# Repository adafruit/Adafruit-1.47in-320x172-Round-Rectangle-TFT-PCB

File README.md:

## Adafruit Adafruit 1.47" 320x172 Round Rectangle Color IPS TFT Display - ST7789 PCB

<a href="http://www.adafruit.com/products/5393"><br/>
Click here to purchase one from the Adafruit shop</a>

PCB files for the Adafruit Adafruit 1.47" 320x172 Round Rectangle Color IPS TFT Display - ST7789. 

Format is EagleCAD schematic and board layout
* https://www.adafruit.com/product/5393

### Description

Don't be such a *square* - throw a curveball into your electronics with a curved-edge miniature display. Here's a new "round rect" TFT display - it's 1.47" diagonal and has high-density 250 ppi, 172x320 full-color pixels with IPS any-angle viewing. We've seen displays of this caliber used in smartwatches and small electronic devices, but they've always been MIPI interface. Finally, we found one that is SPI and has a friendly display driver, so it works with any and all microcontrollers or microcomputers!

This lovely little display breakout is the best way to add a small, colorful, and very bright display to any project. Since the display uses 4-wire SPI to communicate and has its own pixel-addressable frame buffer, it can be used with every kind of microcontroller. Even a very small one with low memory and few pins available! The 1.47" display has 172x320 16-bit full color pixels and is an **IPS** display, so the color looks great up to 80 degrees off-axis in any direction. The TFT driver (ST7789) is very similar to the popular ST7735, and our Arduino library supports it well.

Note that the way we get the rounded corners is by *deleting* pixels. The corner pixels are still addressed in RAM, they just don't appear, so it isn't like you have to do some special radial-pixel mapping. Treat it like a rectangular display.

The breakout has the TFT display soldered on (it uses a delicate flex-circuit connector) as well as an ultra-low-dropout 3.3V regulator, auto-reset circuitry, and a 3/5V level shifter so you can use it with 3.3V or 5V power and logic. We also had a little extra space, so we placed a microSD card holder so you can easily load full color bitmaps from a FAT16/FAT32 formatted microSD card. The microSD card is not included, [but you can pick one up here](https://www.adafruit.com/product/5251).

Of course, we wouldn't just leave you with a datasheet and a "good luck!" - [we've written a full open-source graphics Arduino library that can draw pixels, lines, rectangles, circles, text, and bitmaps as well as example code](https://github.com/adafruit/Adafruit-ST7735-Library). The code is written for Arduino but can be easily ported to your favorite microcontroller! Wiring is easy, we strongly encourage using the hardware SPI pins of your Arduino as software SPI is noticeably slower when dealing with this size display. [For Raspberry Pi or other Single Board Computer Python users, we have a user-space Pillow-compatible library](https://github.com/adafruit/Adafruit_CircuitPython_RGB_Display). For [CircuitPython there's a displayio driver for native support](https://github.com/adafruit/Adafruit_CircuitPython_ST7789).

This display breakout also features an 18-pin "EYE SPI" standard FPC connector with a flip-top connector. You can use an 18-pin 0.5mm pitch FPC cable to connect to all the GPIO pins, for when you want to skip the soldering.

**Please note!** This display is designed original for smartwatches and similar, where there's a glass over the screen. Without something gently holding the screen down, the backlight can eventually peel away from the TFT. (It's not destructive but it's unattractive) You can prevent this by, ideally, adding a plastic or glass cover/overlay. If using bare, try dabbing a touch of E6000 or similar craft glue on the thin side edges, or using a thin piece of tape to keep the front TFT attached to the backlight.

### License

Adafruit invests time and resources providing this open source design, please support Adafruit and open-source hardware by purchasing products from [Adafruit](https://www.adafruit.com)!

Designed by Limor Fried/Ladyada for Adafruit Industries.

Creative Commons Attribution/Share-Alike, all text above must be included in any redistribution. 
See license.txt for additional details.

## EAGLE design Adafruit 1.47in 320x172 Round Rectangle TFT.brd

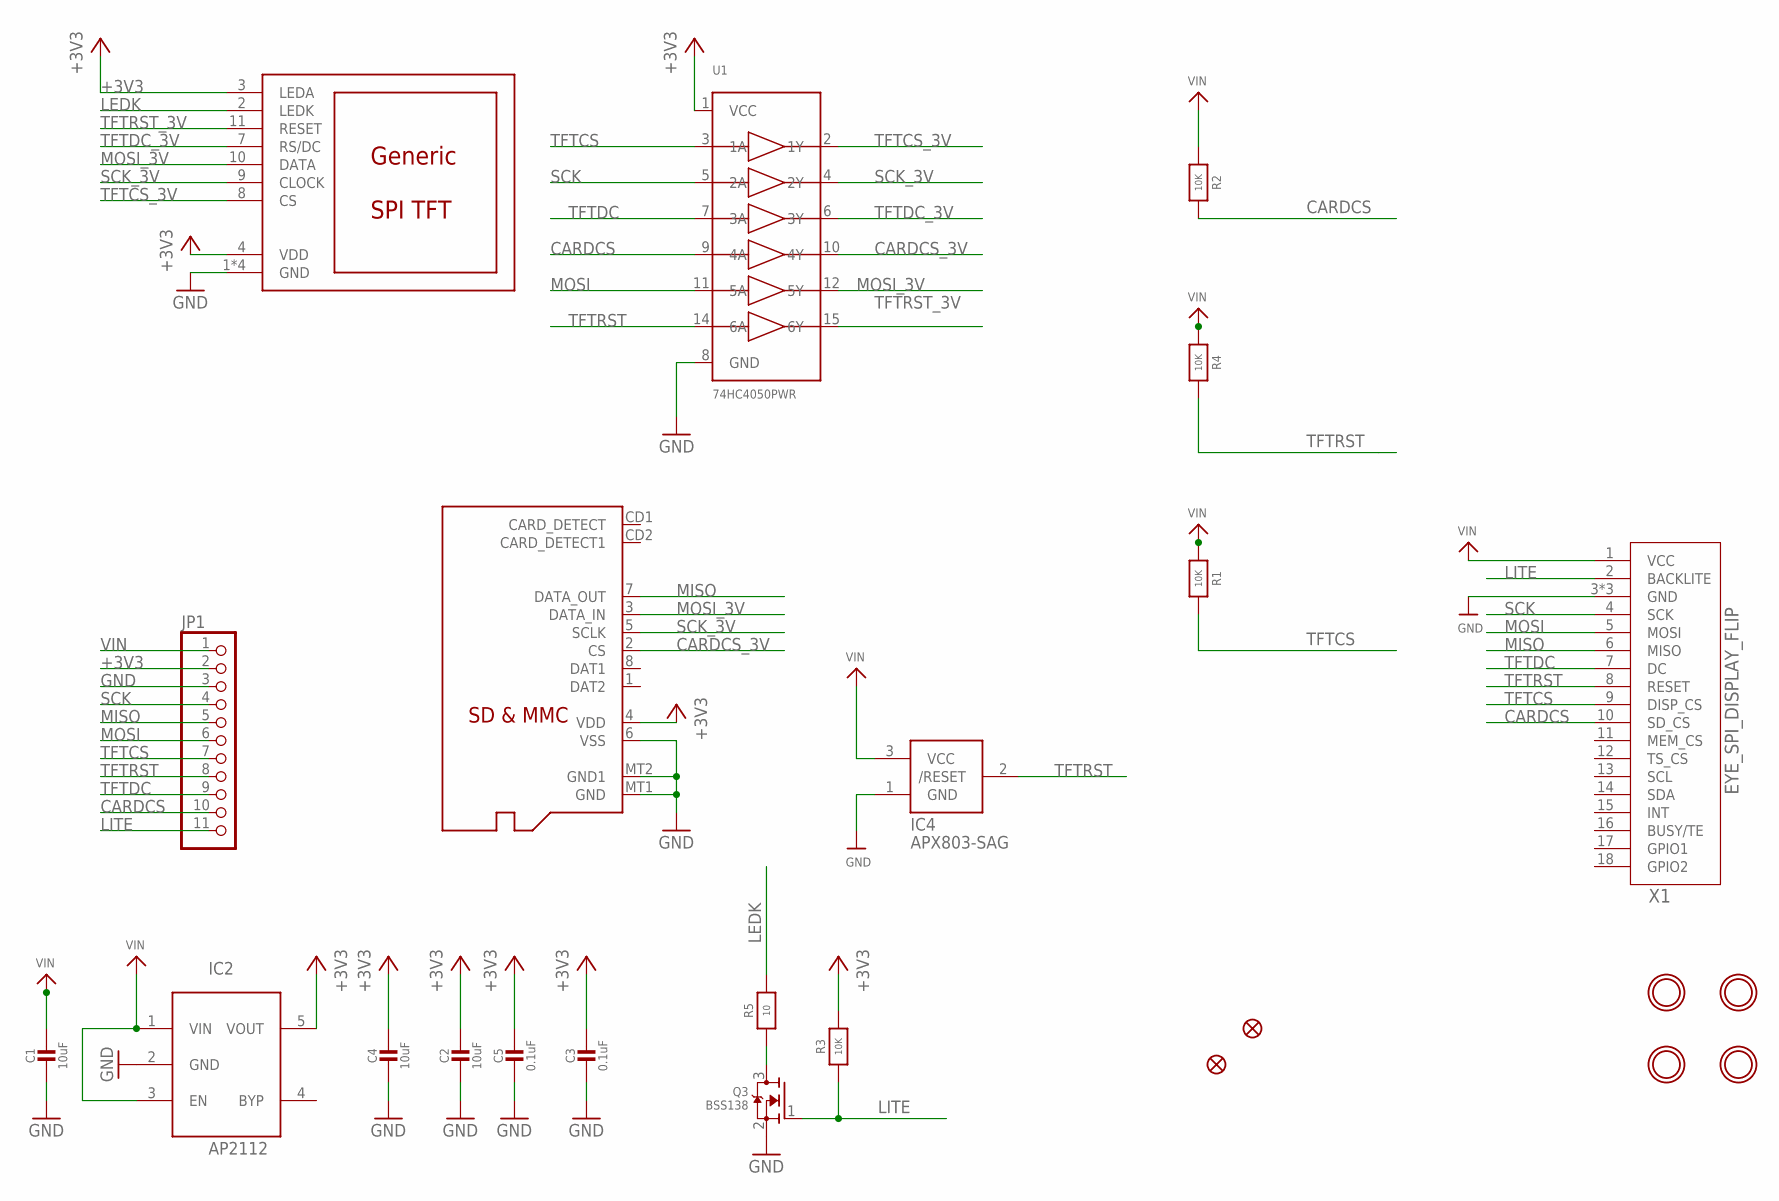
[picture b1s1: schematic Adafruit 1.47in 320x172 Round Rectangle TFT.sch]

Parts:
C1, C2, C4: 10uF; 0805-NO
C3, C5: 0.1uF; 0603-NO
DISP1: DISP_LCD_GENERIC_SPI_1.47IN_172X320_12P_WRAPUNDER; TFT_1.47IN_172X320_12P
IC2: AP2112; SOT23-5L
IC4: APX803-SAG; SOT23
JP1: HEADER-1X1176MIL; 1X11_ROUND_76
Q2: MICROSD
Q3: BSS138; SOT23-WIDE
R1, R2, R3, R4: 10K; 0603-NO
R5: 10; 0603-NO
U1: 74HC4050PWR; TSSOP16
U$4, U$5: FIDUCIAL_1MM
U$7, U$8, U$9, U$10: MOUNTINGHOLE2.5; MOUNTINGHOLE_2.5_PLATED
X1: EYE_SPI_DISPLAY_FLIP; EYE_SPI_DISPLAY_BOTCONTACT

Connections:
+3V3: C2.1, C3.1, C4.1, C5.1, DISP1.3 (LEDA), DISP1.4 (VDD), IC2.5 (VOUT), JP1.2, Q2.4 (VDD), R3.2, U1.1 (VCC)
CARDCS: JP1.10, R2.1, U1.9 (4A), X1.10 (SD_CS)
CARDCS_3V: Q2.2 (CS), U1.10 (4Y)
GND: C1.2, C2.2, C3.2, C4.2, C5.2, DISP1.1 (GND), DISP1.5 (GND), DISP1.6 (GND), DISP1.12 (GND), IC2.2 (GND), IC4.1 (GND), JP1.3, Q2.6 (VSS), Q2.MT1 (GND), Q2.MT2 (GND1), Q3.2 (S), U1.8 (GND), X1.3 (GND), X1.SUPPORT1 (GND), X1.SUPPORT2 (GND)
LEDK: DISP1.2 (LEDK), R5.2
LITE: JP1.11, Q3.1 (G), R3.1, X1.2 (BACKLITE)
MISO: JP1.5, Q2.7 (DATA_OUT), X1.6 (MISO)
MOSI: JP1.6, U1.11 (5A), X1.5 (MOSI)
MOSI_3V: DISP1.10 (DATA), Q2.3 (DATA_IN), U1.12 (5Y)
unnamed: Q3.3 (D), R5.1
SCK: JP1.4, U1.5 (2A), X1.4 (SCK)
SCK_3V: DISP1.9 (CLOCK), Q2.5 (SCLK), U1.4 (2Y)
TFTCS: JP1.7, R1.1, U1.3 (1A), X1.9 (DISP_CS)
TFTCS_3V: DISP1.8 (CS), U1.2 (1Y)
TFTDC: JP1.9, U1.7 (3A), X1.7 (DC)
TFTDC_3V: DISP1.7 (RS/DC), U1.6 (3Y)
TFTRST: IC4.2 (/RESET), JP1.8, R4.1, U1.14 (6A), X1.8 (RESET)
TFTRST_3V: DISP1.11 (RESET), U1.15 (6Y)
VIN: C1.1, IC2.1 (VIN), IC2.3 (EN), IC4.3 (VCC), JP1.1, R1.2, R2.2, R4.2, X1.1 (VCC)

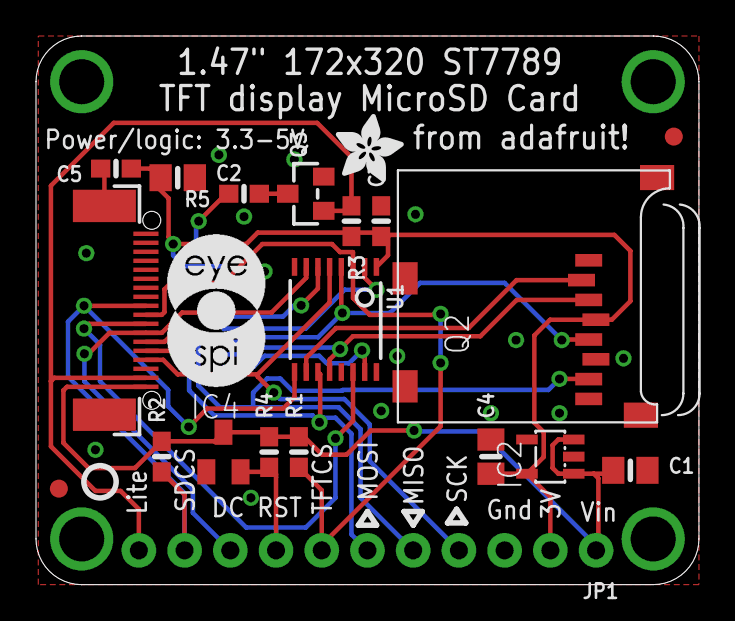
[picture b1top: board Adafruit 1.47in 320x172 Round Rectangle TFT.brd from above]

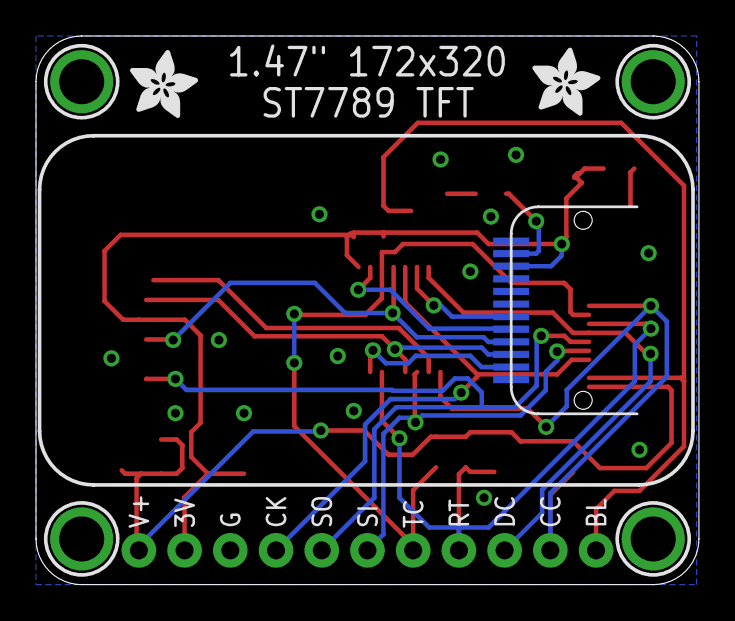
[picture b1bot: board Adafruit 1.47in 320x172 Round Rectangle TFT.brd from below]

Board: 2 copper layers, 36.8 x 30.5 mm, 29 parts (7 on the bottom side), 19 nets.

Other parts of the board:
U$1, U$20, U$21: ADAFRUIT_3.5MM
U$2: PCBFEAT-REV-040
U$22: EYESPI_MINI_LOGO

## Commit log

2022-03-28 Added files
2022-03-28 Fix spacing

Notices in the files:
parts and their libraries:
microbuilder: This work is placed in the public domain, and may be freely used for commercial and non-commercial work with the following conditions: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
